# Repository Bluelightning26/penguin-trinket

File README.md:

# Penguin Trinket

## A Penguin Shaped PCB Trinket
---

### What?

A penguin shaped trinket! There are three LEDs that turn on when the photoresistor detects the absense of light; by using a NOT gate. There is a fourth override LED that can be activated by pressing the push-button. All four LEDs will shine when the button is pressed. Along with the LED glowing, the motor will be activated when the button is pressed. Capacitors are utilized to help store electrical energy, and resistors are used to limit the amount of energy going through the LEDs at a given time. Three NPN resistors are used, one of which is for the NOT gate.

### BOM

| Component | Quantity | Value |
| ----- | ----- | ----- |
| Resistor | 3 | 2x 220Ω / 1x 4.7kΩ
| Capacitor | 2 | 10uF
| Potentiometer | 1 |
| Pushbutton | 1 |
| LED | 4 |
| NPN Transistor | 3 |
| Battery Holder | 2 |
| CR2032 Battery Cell | 2 | 3v
| Photoresistor | 1 |
| Pushbutton | 1 |
| Mini Motor Disk | 1 |

### Graphics: PCB, Schematic, 3d Renders*

 **The potentiometer does not render in the 3d models*

Designed for **Solder**, a YSWS by Hack Club! Learn more [here](https://solder.hackclub.com/)

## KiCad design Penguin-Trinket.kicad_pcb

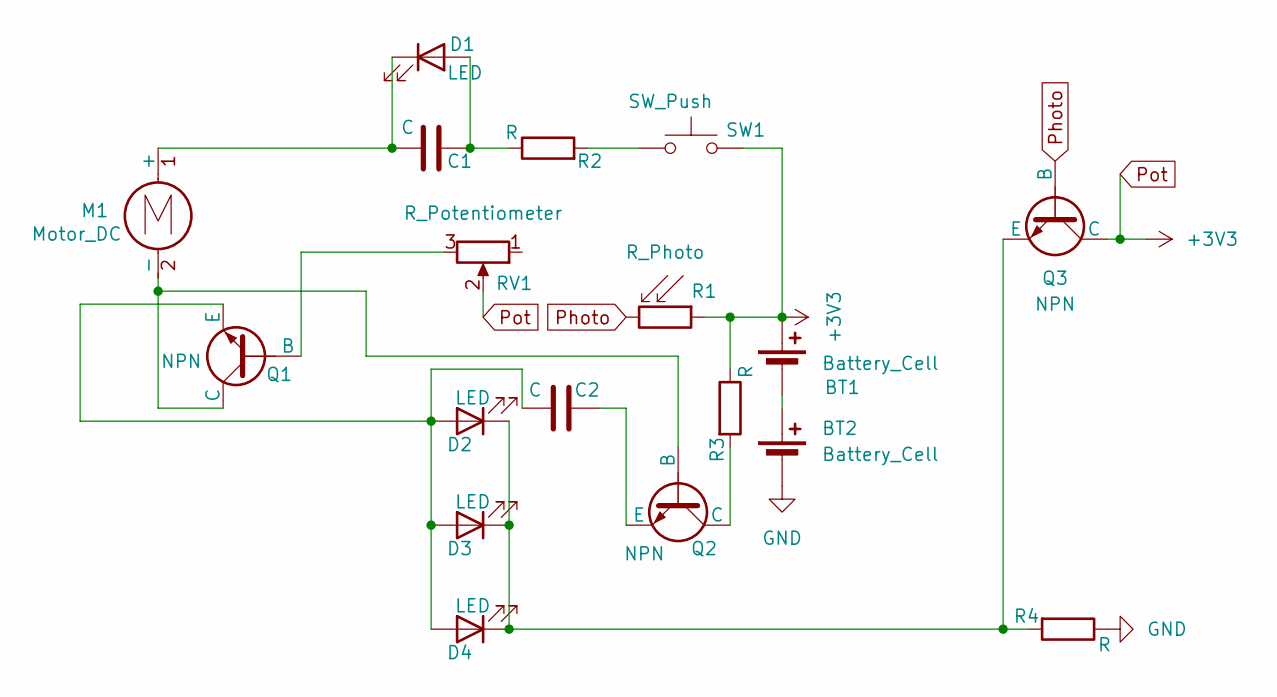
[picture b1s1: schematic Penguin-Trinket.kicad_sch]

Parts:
BT1, BT2: Battery_Cell; BatteryHolder_Keystone_3034_1x20mm
C1, C2: C; CP_Radial_D8.0mm_P5.00mm
D1, D2, D3, D4: LED; LED_D5.0mm
M1: Motor_DC; PinHeader_1x02_P2.54mm_Vertical
Q1, Q2, Q3: NPN; TO-92L_HandSolder
R1: R_Photo; R_LDR_5.1x4.3mm_P3.4mm_Vertical
R2, R3, R4: R; R_Axial_DIN0207_L6.3mm_D2.5mm_P7.62mm_Horizontal
RV1: R_Potentiometer; Potentiometer_Vishay_T73YP_Vertical
SW1: SW_Push; SW_PUSH_6mm

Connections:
GND: BT2.2 (-), R4.1
unnamed: BT1.2 (-), BT2.1 (+)
unnamed: C1.1, D1.2 (A), R2.1
unnamed: C1.2, D1.1 (K), M1.1 (+)
unnamed: C2.1, D2.2 (A), D3.2 (A), D4.2 (A), Q1.3 (E)
unnamed: D2.1 (K), D3.1 (K), D4.1 (K), Q3.3 (E), R4.2
unnamed: M1.2 (-), Q1.1 (C), Q2.2 (B)
unnamed: Q1.2 (B), RV1.3
unnamed: Q2.1 (C), R3.2
unnamed: C2.2, Q2.3 (E)
unnamed: R2.2, SW1.1
Photo: Q3.2 (B), R1.2
Pot: BT1.1 (+), Q3.1 (C), R1.1, R3.1, RV1.2, SW1.2

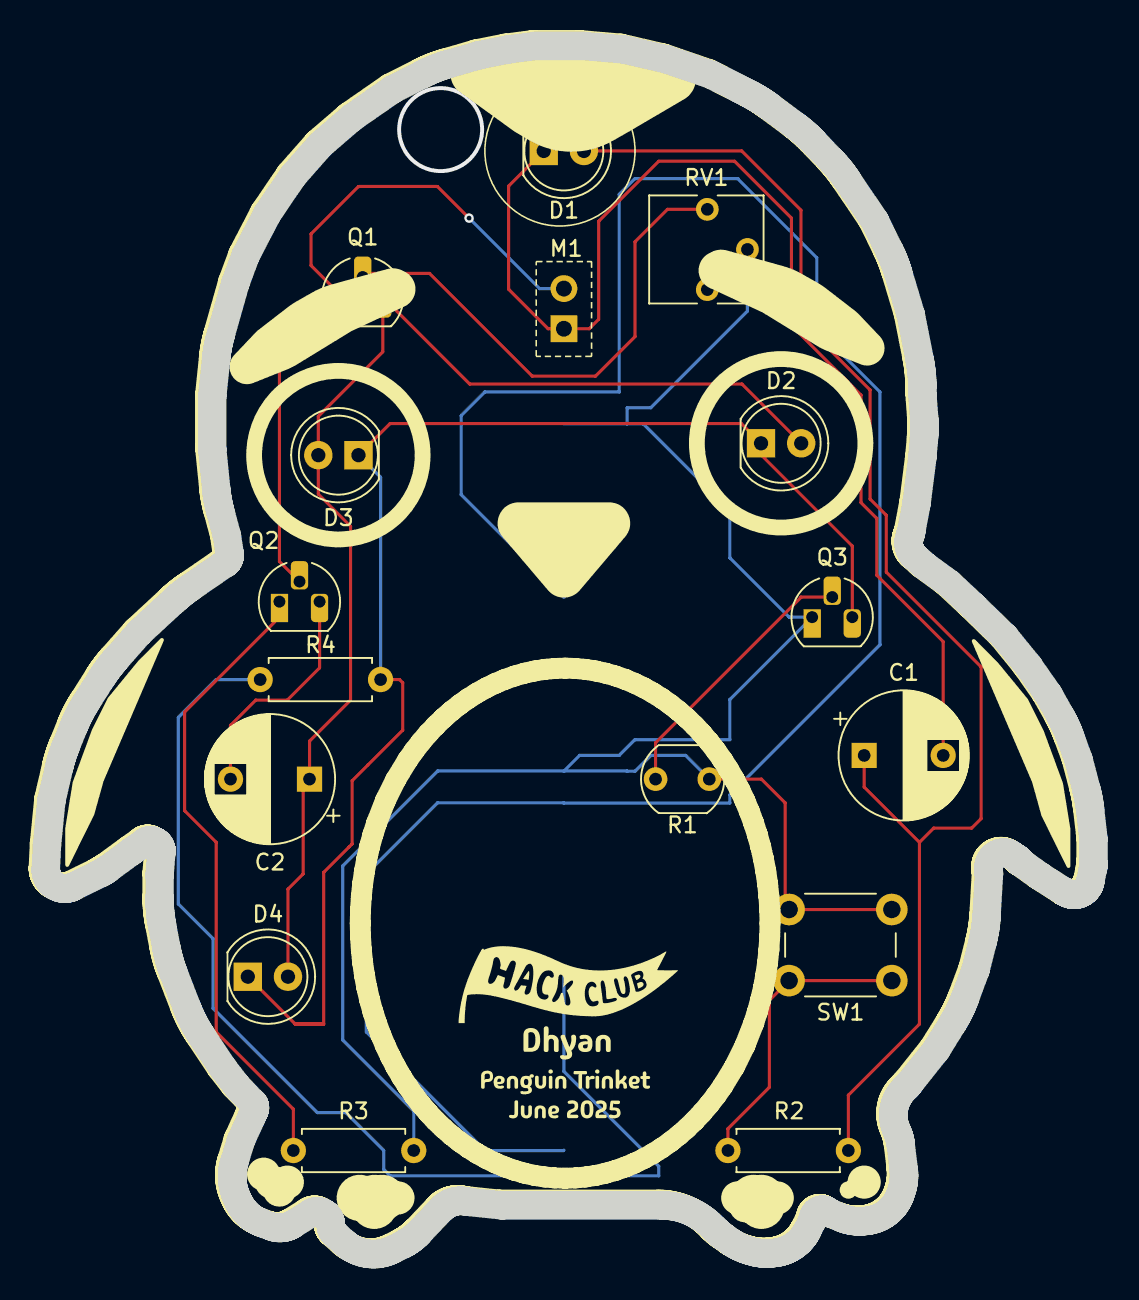
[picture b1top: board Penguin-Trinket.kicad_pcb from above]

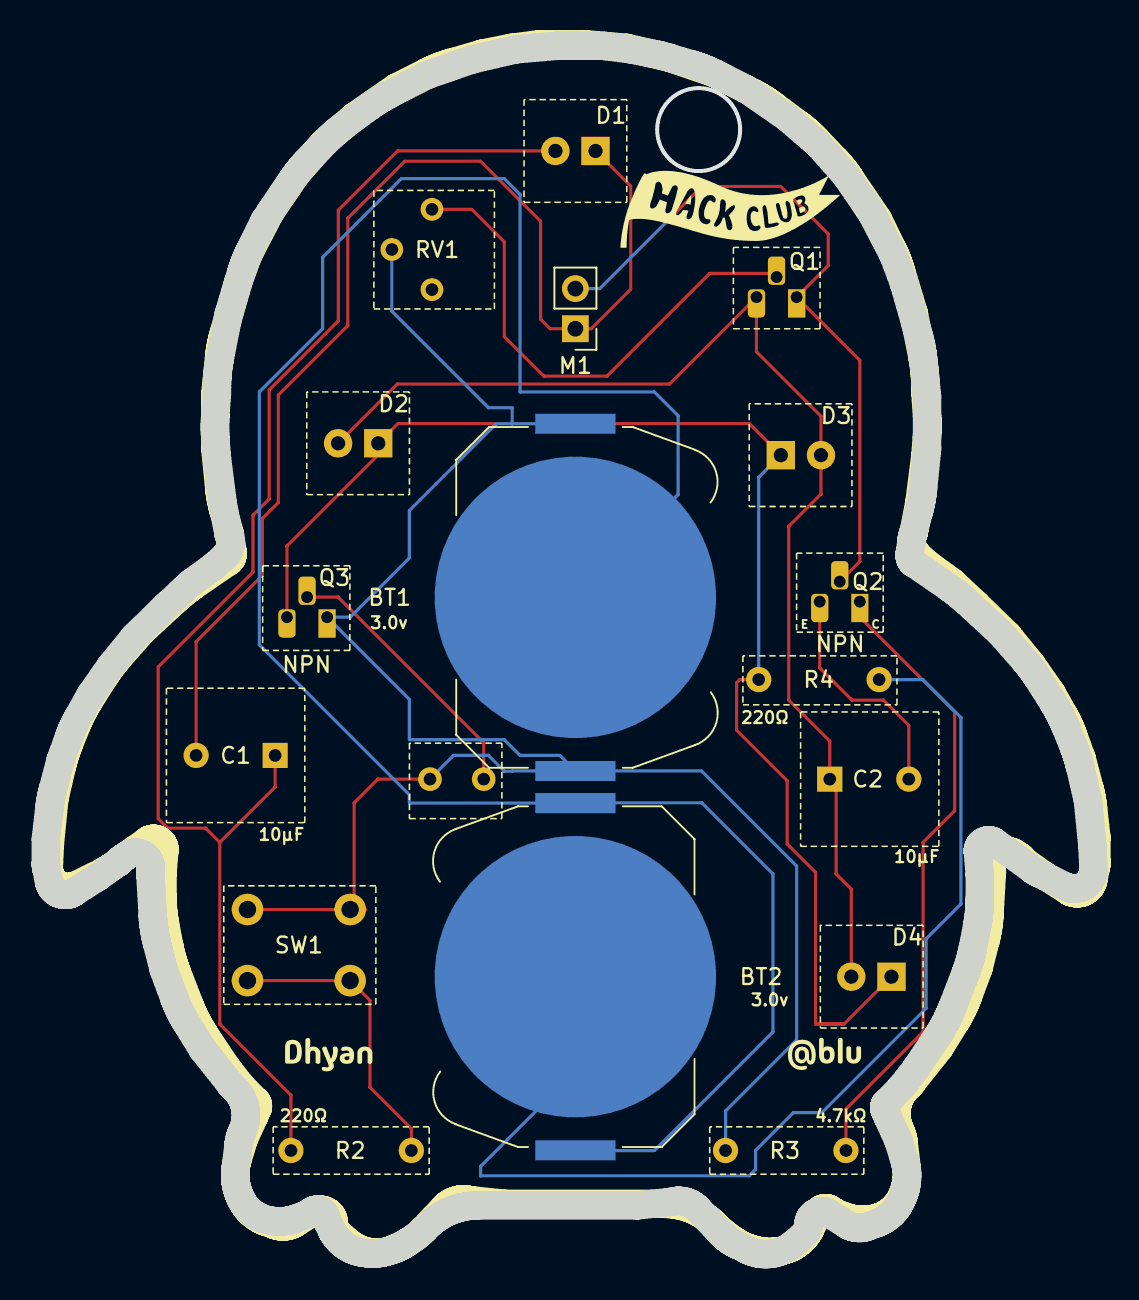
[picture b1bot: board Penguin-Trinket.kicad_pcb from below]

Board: 2 copper layers, 66.3 x 76.5 mm, 18 parts (3 on the bottom side), 13 nets.

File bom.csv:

"Id";"Designator";"Footprint";"Quantity";"Designation";"Supplier and ref";
1;"C1,C2";"CP_Radial_D8.0mm_P5.00mm";2;"C";;;
2;"D2,D3,D4,D1";"LED_D5.0mm";4;"LED";;;
3;"RV1";"Potentiometer_Vishay_T73YP_Vertical";1;"R_Potentiometer";;;
4;"R4,R3,R2";"R_Axial_DIN0207_L6.3mm_D2.5mm_P7.62mm_Horizontal";3;"R";;;
5;"Q1,Q3,Q2";"TO-92L_HandSolder";3;"NPN";;;
6;"SW1";"SW_PUSH_6mm";1;"SW_Push";;;
7;"R1";"R_LDR_5.1x4.3mm_P3.4mm_Vertical";1;"R_Photo";;;
8;"BT1,BT2";"BatteryHolder_Keystone_3034_1x20mm";2;"Battery_Cell";;;
9;"M1";"PinHeader_1x02_P2.54mm_Vertical";1;"Motor_DC";;;

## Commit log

2025-06-08 finally
2025-06-08 keychain hole img
2025-06-17 redo (trinket v3)
    hopefully everything works
